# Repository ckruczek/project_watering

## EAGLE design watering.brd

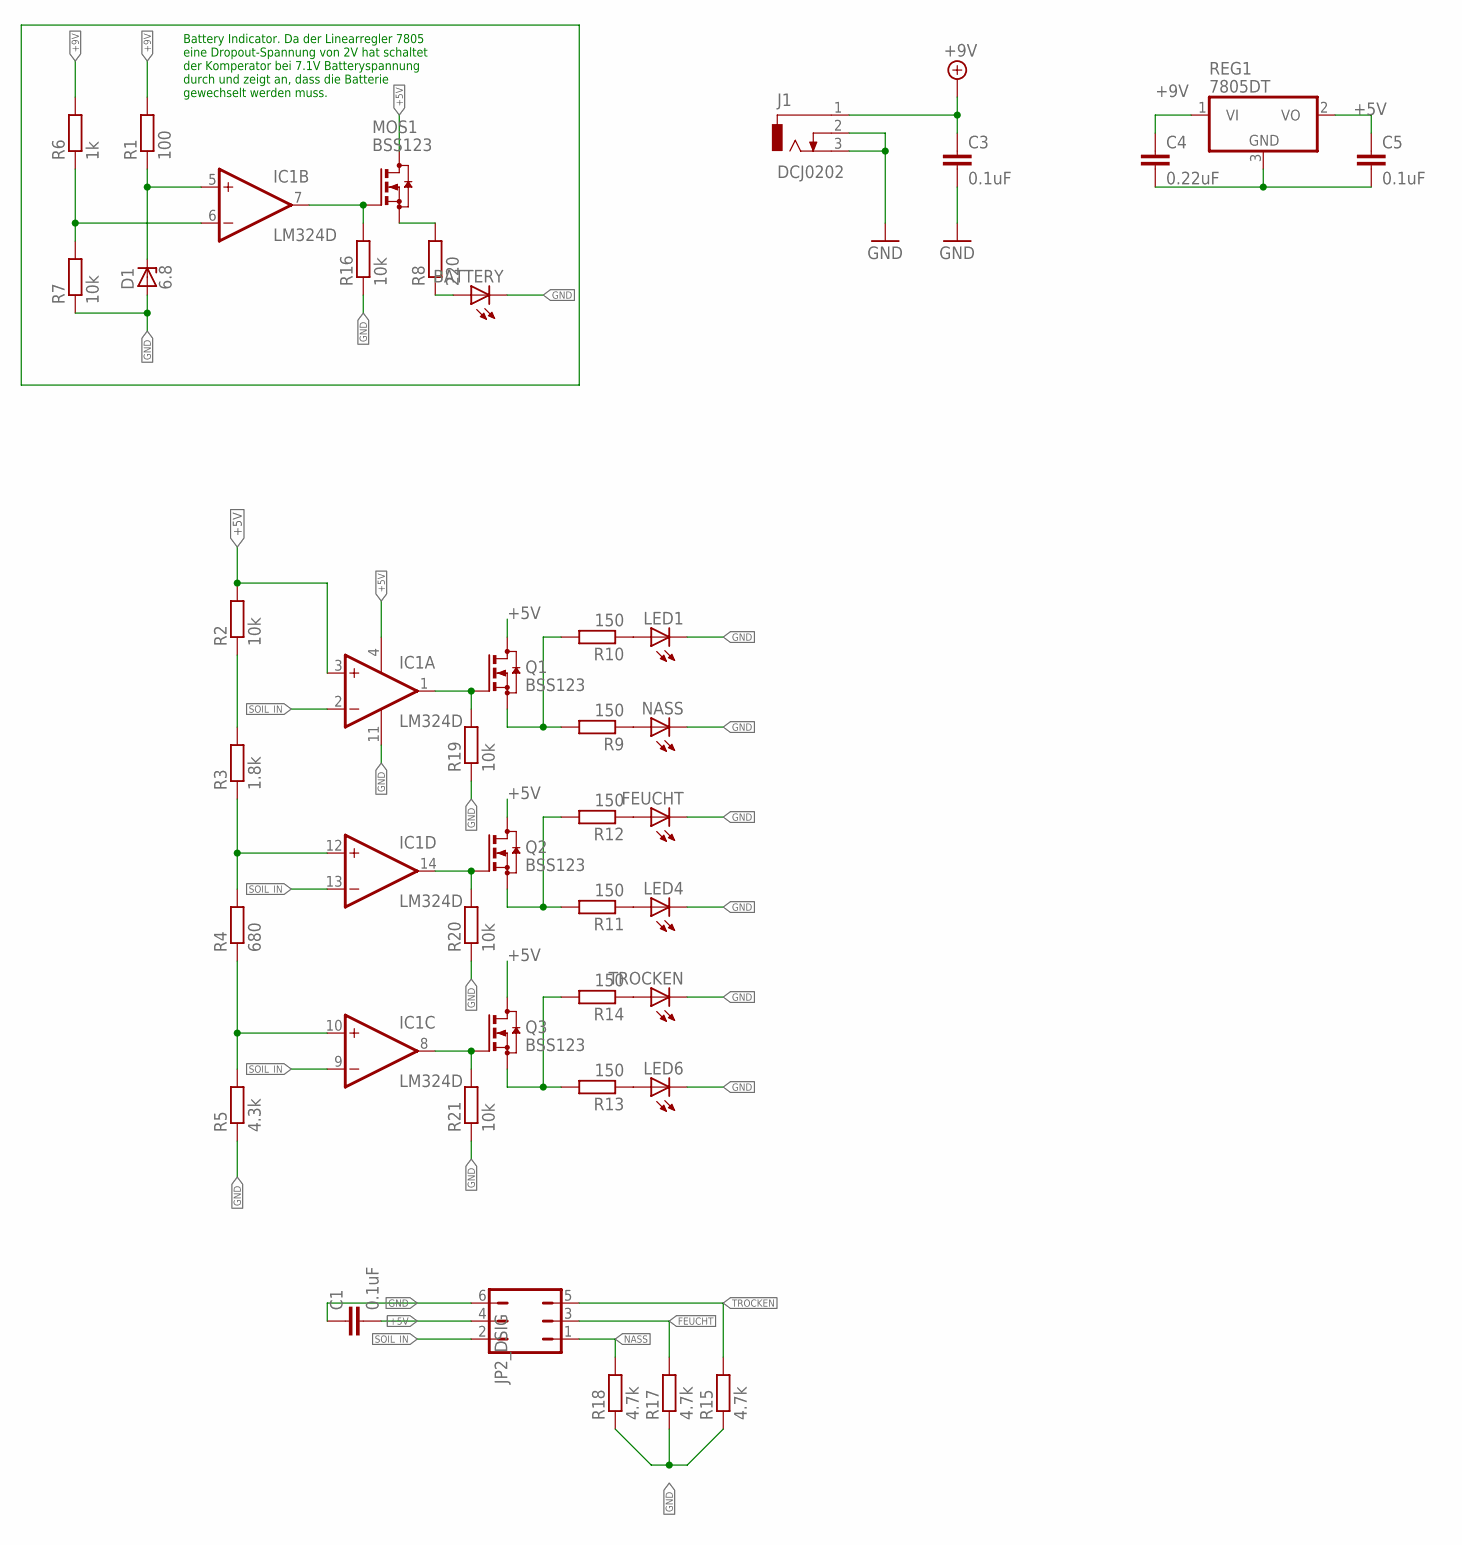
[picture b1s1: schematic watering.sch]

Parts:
BATTERY: LEDSML0805; SML0805
C1, C3, C5: 0.1uF; C0805
C4: 0.22uF; C0805
D1: 6.8; SMB
FEUCHT: LEDSML0805; SML0805
IC1: LM324D; SO14
J1: DCJ0202
JP1: JP2_DSIG; JP3Q
LED1, LED4, LED6: LEDSML0805; SML0805
MOS1: BSS123; SOT23
NASS: LEDSML0805; SML0805
Q1, Q2, Q3: BSS123; SOT23
R1: 100; M0805
R2, R7, R16, R19, R20, R21: 10k; M0805
R3: 1.8k; M0805
R4: 680; M0805
R5: 4.3k; M0805
R6: 1k; M0805
R8: 220; M0805
R9, R10, R11, R12, R13, R14: 150; M0805
R15, R17, R18: 4.7k; M0805
REG1: 7805DT; TO252
TROCKEN: LEDSML0805; SML0805

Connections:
+5V: C1.2, C5.1, IC1.3 (+IN), IC1.4 (V+), JP1.4, MOS1.3 (D), Q1.3 (D), Q2.3 (D), Q3.3 (D), R2.2, REG1.2 (VO)
+9V: C3.1, C4.1, J1.1, R1.2, R6.2, REG1.1 (VI)
FEUCHT: JP1.3, Q2.2 (S), R11.2, R12.2, R17.2
GND: BATTERY.C, C1.1, C3.2, C4.2, C5.2, D1.A, FEUCHT.C, IC1.11 (V-), J1.2, J1.3, JP1.6, LED1.C, LED4.C, LED6.C, NASS.C, R5.1, R7.1, R15.1, R16.1, R17.1, R18.1, R19.1, R20.1, R21.1, REG1.3 (GND), TROCKEN.C
unnamed: R2.1, R3.2
unnamed: IC1.1 (OUT), Q1.1 (G), R19.2
unnamed: D1.C, IC1.5 (+IN), R1.1
unnamed: IC1.14 (OUT), Q2.1 (G), R20.2
unnamed: IC1.8 (OUT), Q3.1 (G), R21.2
unnamed: IC1.6 (-IN), R6.1, R7.2
unnamed: IC1.7 (OUT), MOS1.1 (G), R16.2
unnamed: MOS1.2 (S), R8.2
unnamed: BATTERY.A, R8.1
unnamed: LED1.A, R10.1
unnamed: IC1.12 (+IN), R3.1, R4.2
unnamed: IC1.10 (+IN), R4.1, R5.2
unnamed: NASS.A, R9.1
unnamed: FEUCHT.A, R12.1
unnamed: LED4.A, R11.1
unnamed: R14.1, TROCKEN.A
unnamed: LED6.A, R13.1
NASS: JP1.1, Q1.2 (S), R9.2, R10.2, R18.2
SOIL_IN: IC1.2 (-IN), IC1.9 (-IN), IC1.13 (-IN), JP1.2
TROCKEN: JP1.5, Q3.2 (S), R13.2, R14.2, R15.2

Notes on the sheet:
Battery Indicator. Da der Linearregler 7805 eine Dropout-Spannung von 2V hat schaltet der Komperator bei 7.1V Batteryspannung durch und zeigt an, dass die Batterie gewechselt werden muss.

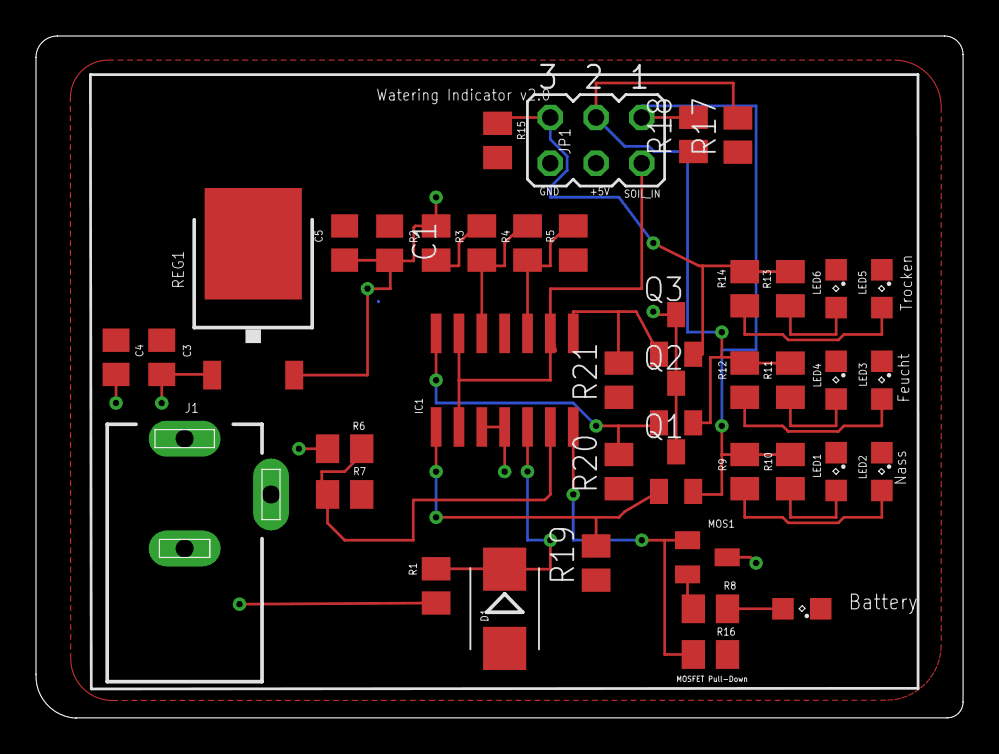
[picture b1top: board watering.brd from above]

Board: 2 copper layers, 51.5 x 37.9 mm, 42 parts (0 on the bottom side), 24 nets.

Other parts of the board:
DRILEGEND: DRILEGEND

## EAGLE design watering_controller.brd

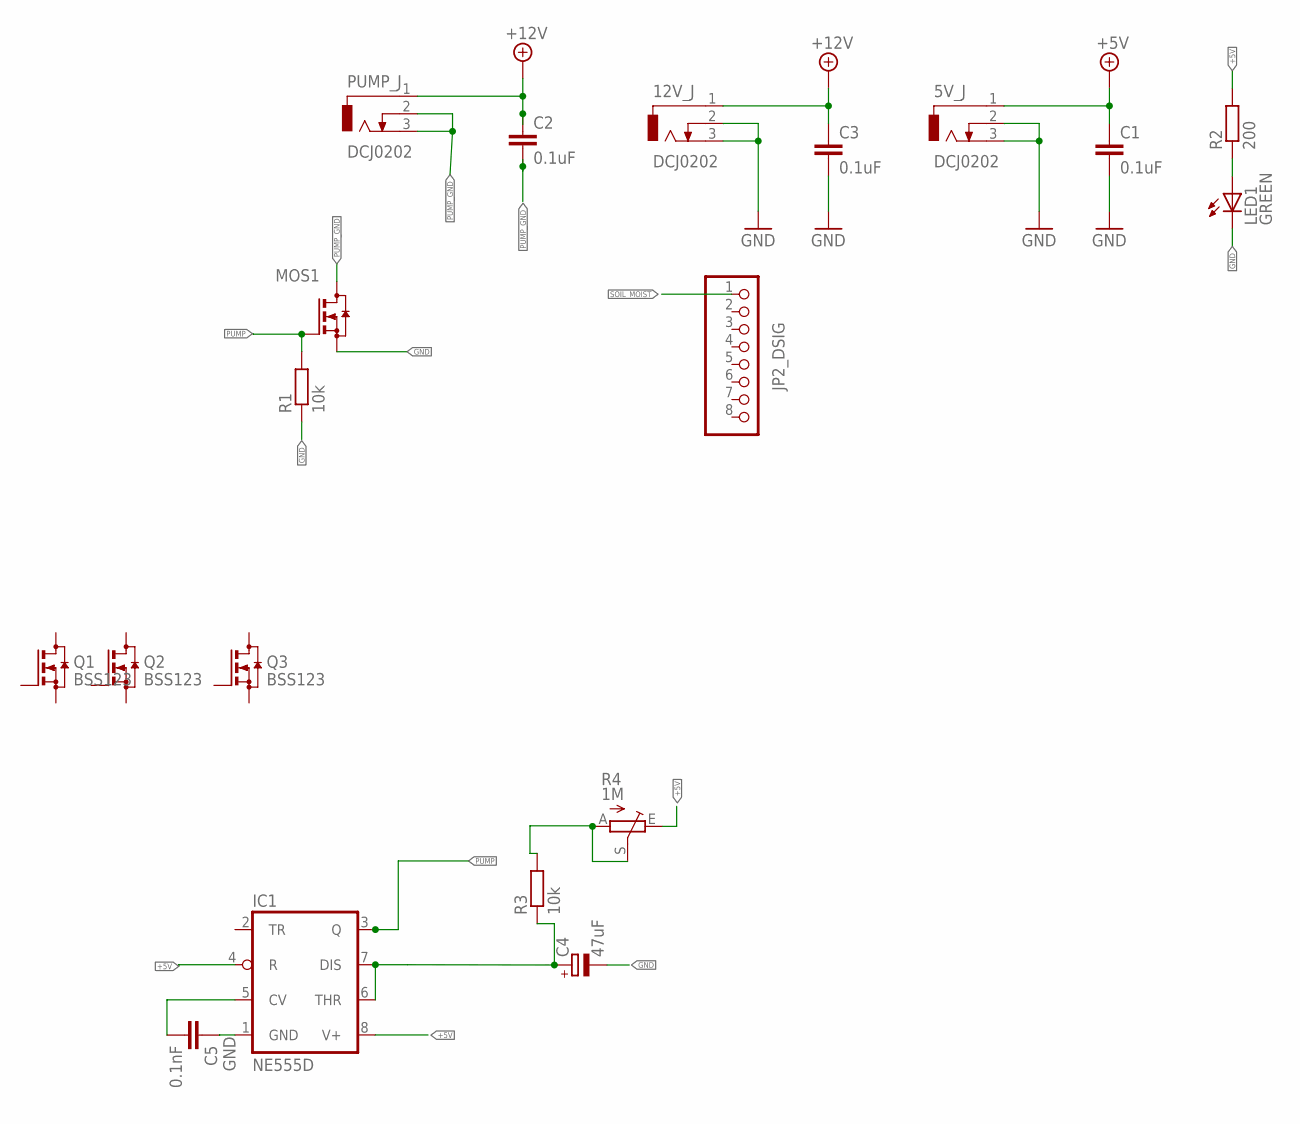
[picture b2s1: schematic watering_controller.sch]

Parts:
5V_J, 12V_J: DCJ0202
C1, C2, C3: 0.1uF; C0805
C4: 47uF; A/3216-18R
C5: 0.1nF; C0805
IC1: NE555D; SO08
JP1: JP2_DSIG; 1X08
LED1: GREEN; SML0805
MOS1: FDN359BN; SOT23
PUMP_J: DCJ0202
Q1, Q2, Q3: BSS123; SOT23
R1, R3: 10k; M0805
R2: 200; M0805
R4: 1M; B25P

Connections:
+5V: IC1.4 (R), IC1.8 (V+), R2.2, R4.E
+9V: 5V_J.1, 12V_J.1, C1.1, C2.1, C3.1, PUMP_J.1
GND: 5V_J.2, 5V_J.3, 12V_J.2, 12V_J.3, C1.2, C3.2, C4.-, C5.1, IC1.1 (GND), LED1.C, MOS1.2 (S), R1.1
unnamed: C5.2, IC1.5 (CV)
unnamed: R3.2, R4.A, R4.S
unnamed: C4.+, IC1.6 (THR), IC1.7 (DIS), R3.1
unnamed: LED1.A, R2.1
PUMP: IC1.3 (Q), MOS1.1 (G), R1.2
PUMP_GND: C2.2, MOS1.3 (D), PUMP_J.2, PUMP_J.3
SOIL_MOIST: JP1.1

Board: 2 copper layers, 19 parts (0 on the bottom side), 9 nets, no tracks yet.

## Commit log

2017-06-29 Remove LED labels and reorganised battery indicator to shrinken the design.
2017-06-29 Update positions and labels for silkscreen
2017-06-30 Update parts and pcb image
2017-07-02 Add pull-down resistor for MOSFET and changed MOSFET type to IRLZ44N
2017-07-09 Update drill files for production
2017-08-02 Create watering indicator v2.0 for SMD
2017-09-01 Update smd version
2017-09-01 Update smd image
2017-09-02 Replace BJT to MOSFET for led switching
2017-09-08 Change zener diode package
